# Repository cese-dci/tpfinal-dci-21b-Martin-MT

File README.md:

## Trabajo práctico final de la asignatura DCI ##
Este repositorio contiene el trabajo práctico final para la asignatura de Diseño de Circuitos Impresos de la carrera de posgrado de FIUBA.

* Autor: Martín Mello Teggia
* Título corto del trabajo:  Réplica pro mini signal generator
* Descripción:  Réplica del un módulo para Arduino para generación de señales.

## Licencia de este trabajo ##
XXXMENCIONAR ACÁ LA LICENCIAXXX (Editar este párrafo) 
Y además colcar el archivo de texto de la misma en el directorio raíz.
Para este TP se pide que la licencia sea de hardware abierto.
Ver la sección "What license should I use?": https://www.oshwa.org/faq/

## Estructura del TP FINAL ##

Se propone y se pide utilizar la siguiente estructura.

* doc: Toda la información sobre el circuito, principalmente de autoría o procesamiento propio. Por ejemplo:
  * Notas de ingeniería propias.
  * Notas de aplicación propias.
  * Estudios previos, estado del arte, resumen de las investigaciones.
  * Notas con cálculos.
  * Dibujos adicionales.
  * Fotos de los prototipos.
  * Presupuestos, cotizaciones.
* info: Toda la iformación recolectada, principalmente de terceros, como por ejemplo:
  * Hojas de datos.
  * Notas de aplicación.
  * Info de productos comerciales.
  * Info en internet.
* pcb: Archivos de diseño esquemático y pcb.

Dependiendo la magnitud del proyecto, tendremos más o menos información en estos directorios. 
Revisar los README.md en cada directorio para conocer las pautas de cada uno para este TP.

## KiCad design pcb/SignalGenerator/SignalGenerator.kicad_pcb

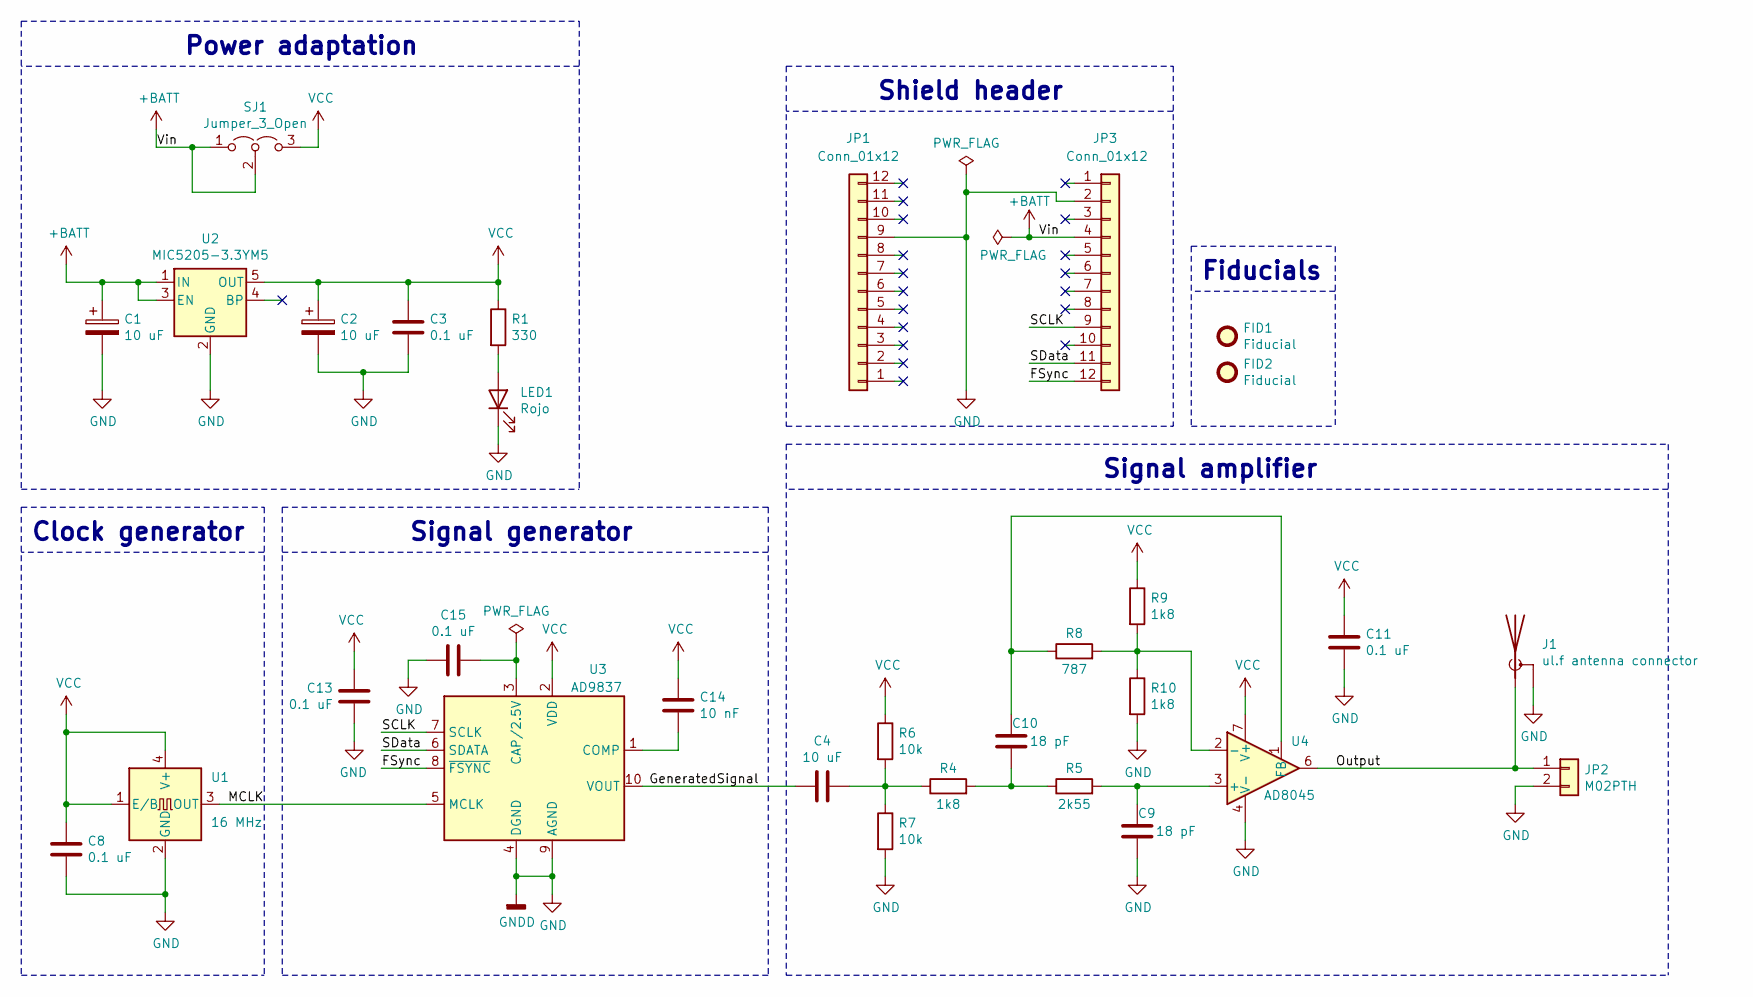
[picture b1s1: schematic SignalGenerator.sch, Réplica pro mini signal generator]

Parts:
C1, C2: 10 uF; CP_EIA-3528-12_Kemet-T
C3, C8, C11, C13, C15: 0.1 uF; C_0603_1608Metric
C4: 10 uF; C_0603_1608Metric
C9, C10: 18 pF; C_0603_1608Metric
C14: 10 nF; C_0603_1608Metric
FID1, FID2: Fiducial; Fiducial_0.5mm_Mask1mm
J1: ul.f antenna connector; coaxial_u.fl-r-smt-1
JP1, JP3: Conn_01x12; PinHeader_1x12_P2.54mm_Vertical
JP2: M02PTH; PinHeader_1x02_P2.54mm_Vertical
LED1: Rojo; LED_0603_1608Metric
R1: 330; R_0603_1608Metric
R4, R9, R10: 1k8; R_0603_1608Metric
R5: 2k55; R_0603_1608Metric
R6, R7: 10k; R_0603_1608Metric
R8: 787; R_0603_1608Metric
SJ1: Jumper_3_Open; SolderJumper-3_P1.3mm_Bridged2Bar12_Pad1.0x1.5mm
U1: 16 MHz; Oscillator_SMD_IQD_IQXO70-4Pin_7.5x5.0mm
U2: MIC5205-3.3YM5; SOT-23-5
U3: AD9837; LFCSP-WD-10-1EP_3x3mm_P0.5mm_EP1.64x2.38mm
U4: AD8045; SOIC-8_3.9x4.9mm_P1.27mm

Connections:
+BATT: C1.1, JP3.4, SJ1.1 (A), SJ1.2 (C), U2.1 (IN), U2.3 (EN)
/FSync: JP3.12, U3.8 (~FSYNC)
/GeneratedSignal: C4.2, U3.10 (VOUT)
/MCLK: U1.3 (OUT), U3.5 (MCLK)
/Output: J1.1 (A), JP2.1, U4.6
/SCLK: JP3.9, U3.7 (SCLK)
/SData: JP3.11, U3.6 (SDATA)
GND: C1.2, C2.2, C3.2, C8.2, C9.2, C11.2, C13.2, C15.2, J1.2 (Shield), JP1.9, JP2.2, JP3.2, LED1.1 (K), R7.2, R10.2, U1.2 (GND), U2.2 (GND), U3.4 (DGND), U3.9 (AGND), U4.4 (V-)
unnamed: C4.1, R4.1, R6.2, R7.1
unnamed: C9.1, R5.2, U4.3 (+)
unnamed: C10.1, R8.1, U4.1 (FB)
unnamed: C10.2, R4.2, R5.1
unnamed: C14.2, U3.1 (COMP)
unnamed: C15.1, U3.3 (CAP/2.5V)
unnamed: LED1.2 (A), R1.2
unnamed: R8.2, R9.2, R10.1, U4.2 (-)
VCC: C2.1, C3.1, C8.1, C11.1, C13.1, C14.1, R1.1, R6.1, R9.1, SJ1.3 (B), U1.1 (E/B), U1.4 (V+), U2.5 (OUT), U3.2 (VDD), U4.7 (V+)

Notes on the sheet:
Clock generator
Signal generator
Signal amplifier
Shield header
Power adaptation
Fiducials

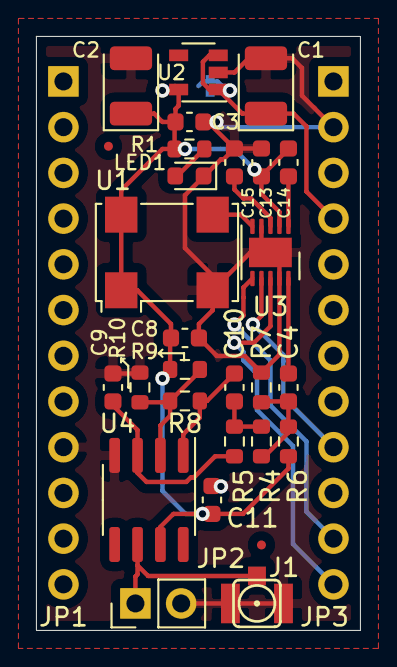
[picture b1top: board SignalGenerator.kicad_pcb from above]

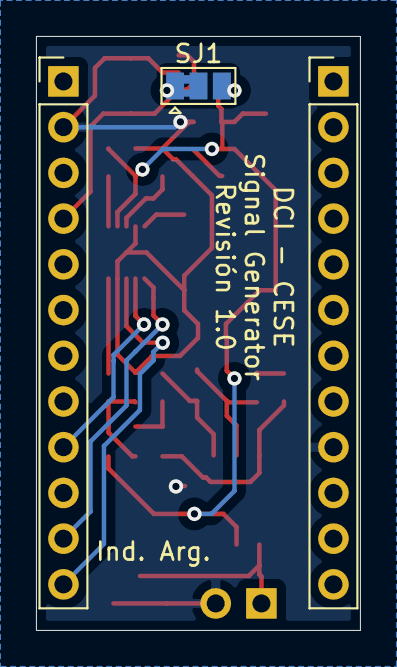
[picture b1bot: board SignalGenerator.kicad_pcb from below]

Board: 2 copper layers, 18.0 x 33.0 mm, 31 parts (3 on the bottom side), 17 nets.

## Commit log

2021-07-05 Agrego archivos iniciales al repositorio
2021-07-05 Agrego documentos solicitados de la propuesta de trabajo a realizar
2021-07-05 Agregados datasheet de componentes, y agregada documentación
2021-07-05 Agrego documento con reglas de diseño del fabricante local
2021-07-26 Agrego esquemático completo, asociación de componentes y modelos 3d completo
2021-08-09 Agrego modelo correcto para U3, y ubicación de los componentes
2021-08-10 Agrego routeo del PCB
2021-08-16 Cambios solicitados por el docente
2021-08-16 Agrego manufacturer, mnf Part Number, Supplier y Supplier PN para los componentes importantes
